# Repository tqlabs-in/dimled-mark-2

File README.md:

# DimLED Mark II

A simple led dimmer based on ESP-01 Module powered by esphome firmware.

Checkout [iBOM](https://htmlpreview.github.io/?https://raw.githubusercontent.com/tqlabs-in/dimled-mark-2/main/output/bom/ibom.html) for more details.

### Renders ( Mark II.b )

### Operating Power

Max Values:

- Max Voltage: 36VDC
- Max Current: 15A
- Max Power: 400W

> Above specs are contstrained by XY-MOS PWM Trigger Module

Recommended Values:

- less than 10A at 12VDC
- less than 6A at 24VDC

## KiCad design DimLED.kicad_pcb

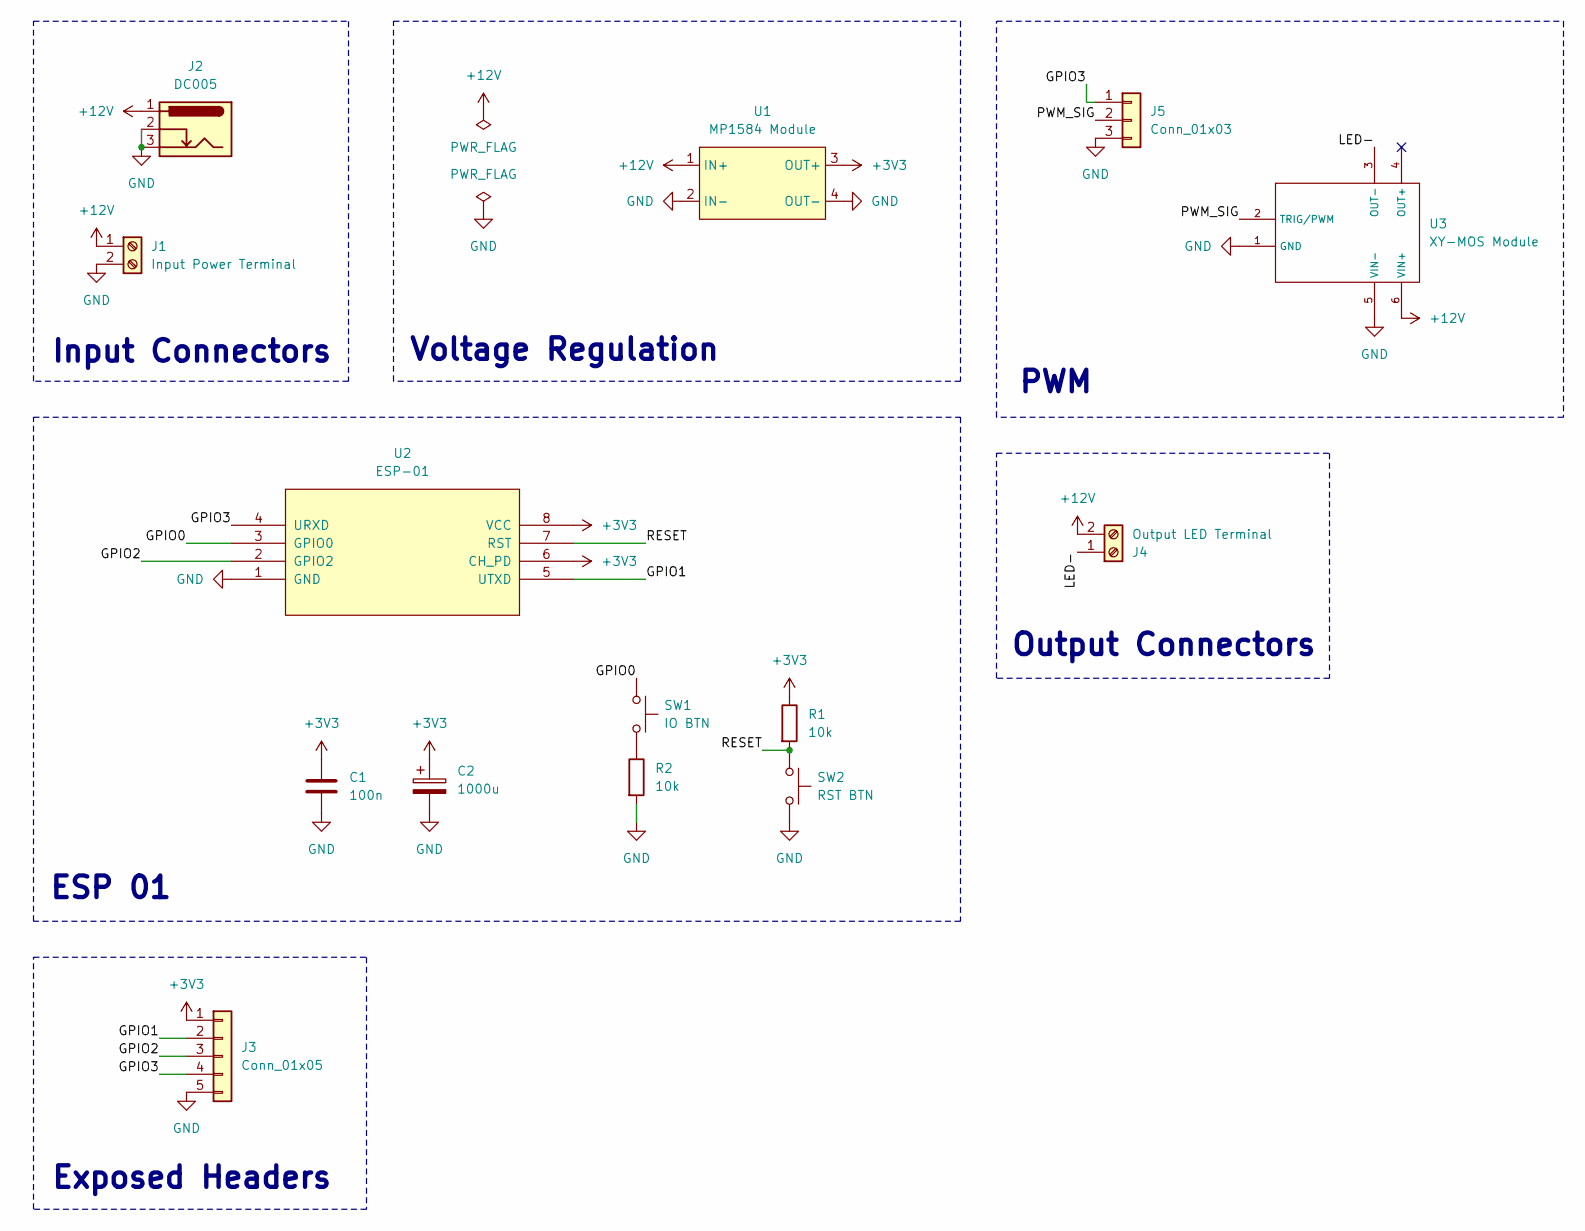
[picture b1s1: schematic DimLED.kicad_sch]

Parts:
C1: 100n; C_Disc_D3.0mm_W2.0mm_P2.50mm
C2: 1000u; CP_Radial_D8.0mm_P3.80mm
J1: Input Power Terminal; TerminalBlock_bornier-2_P5.08mm
J2: DC005
J3: Conn_01x05; PinHeader_1x05_P2.54mm_Vertical
J4: Output LED Terminal; TerminalBlock_bornier-2_P5.08mm
J5: Conn_01x03; PinHeader_1x03_L_Reverse_P2.54mm_Vertical
R1, R2: 10k; R_Axial_DIN0207_L6.3mm_D2.5mm_P7.62mm_Horizontal
SW1: IO BTN; SW_PUSH_6mm
SW2: RST BTN; SW_PUSH_6mm
U1: MP1584 Module; MP1584-Module_22.1x16.8mm_Cutout_Mixed
U2: ESP-01
U3: XY-MOS Module; XY_MOS-Module_Mounted

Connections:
+3V3: C1.1, C2.1, J3.1, R1.1, U1.3 (OUT+), U2.6 (CH_PD), U2.8 (VCC)
+12V: J1.1, J2.1, J4.2, U1.1 (IN+), U3.6 (VIN+)
/GPIO0: SW1.1, U2.3 (GPIO0)
/GPIO1: J3.2, U2.5 (UTXD)
/GPIO2: J3.3, U2.2 (GPIO2)
/GPIO3: J3.4, J5.1, U2.4 (URXD)
/LED-: J4.1, U3.3 (OUT-)
/PWM_SIG: J5.2, U3.2 (TRIG/PWM)
/RESET: R1.2, SW2.1, U2.7 (RST)
GND: C1.2, C2.2, J1.2, J2.2, J2.3, J3.5, J5.3, R2.2, SW2.2, U1.2 (IN-), U1.4 (OUT-), U2.1 (GND), U3.1 (GND), U3.5 (VIN-)
unnamed: R2.1, SW1.2

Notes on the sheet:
Input Connectors
Voltage Regulation
Output Connectors
ESP 01
PWM
Exposed Headers

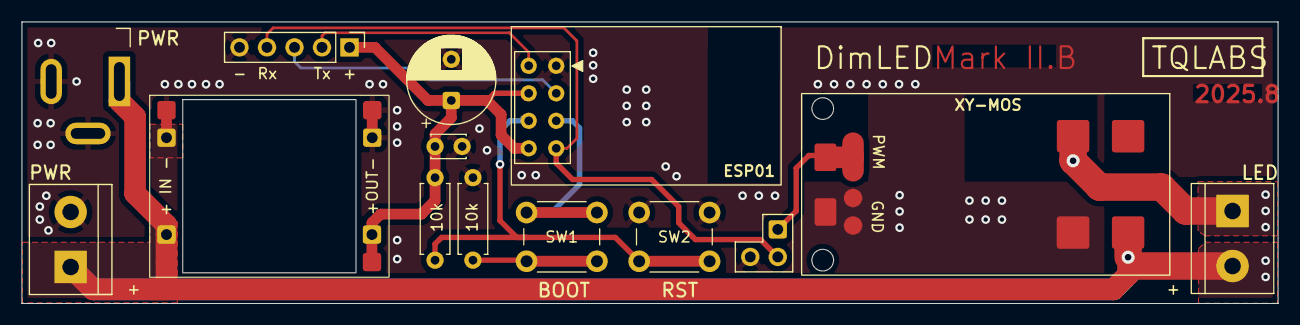
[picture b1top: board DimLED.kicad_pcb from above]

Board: 2 copper layers, 116.0 x 26.0 mm, 14 parts (0 on the bottom side), 11 nets.

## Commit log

2025-09-10 feat: mark II.b
2025-09-10 feat: esphome config
2025-09-10 fix: esphome include paths
2025-09-10 chore: add alternate syntax for package
2025-09-10 docs: update readme
    components already in eBOM
2025-09-10 feat: add ibom
2025-09-11 feat: gerbers
2025-09-16 chore: general update
2025-09-16 fix: bom location
2025-09-17 feat: bottom 12v path
2025-10-04 feat: add license
2026-01-06 chore: remove esphome
    will be moved to another dedicated repo
2026-01-06 docs: move to more open license
2026-01-06 docs: update readme
2026-02-05 revert: remove esphome
    This reverts commit 504cbaec9c05dd88610339bbc449b717c55db564.
2026-02-05 feat: update esphome
